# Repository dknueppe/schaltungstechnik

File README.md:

# Table of Contents

1.  [Aktiver Tiefpassfilter im Rahmen des Schaltungstechnik Praktikums](#org497d46e)
    1.  [Realisierung eines 1kHz Tiefpassfilter mit veränderlicher Verstärkung](#orgdd8e5d2)
    2.  [Bill of Materials](#org9c20808)

# Aktiver Tiefpassfilter im Rahmen des Schaltungstechnik Praktikums

## Realisierung eines 1kHz Tiefpassfilter mit veränderlicher Verstärkung

Der Filter nutzt eine Sallen-Key Topologie und kann mit verschiedenen Spannungsquellen betrieben werden.
Desweiteren lässt sich die Verstärkung über ein Potentiometer verstellen.

Der Jumper ist entsprechend der Spannungsversorgung zu setzen. Auf der Stellung **GND** wird das GND potential
zur Referenzspannung für den Verstärker, somit sollte eine symmetrische Spannungsversorgung genutzt werden.
Auf der Stellung **REF** wird eine interne Referenzspannung genutzt, es ist empfohlen das Spannungsquelle und
Signal in diesem Fall voneinander galvanisch getrennt sind.

## Bill of Materials

<table border="2" cellspacing="0" cellpadding="6" rules="groups" frame="hsides">

<colgroup>
<col  class="org-right" />

<col  class="org-left" />

<col  class="org-left" />

<col  class="org-left" />

<col  class="org-right" />

<col  class="org-left" />

<col  class="org-left" />
</colgroup>
<thead>
<tr>
<th scope="col" class="org-right">Pos</th>
<th scope="col" class="org-left">Item</th>
<th scope="col" class="org-left">Value</th>
<th scope="col" class="org-left">Package</th>
<th scope="col" class="org-right">Qty</th>
<th scope="col" class="org-left">Cost</th>
<th scope="col" class="org-left">Link</th>
</tr>
</thead>

<tbody>
<tr>
<td class="org-right">1</td>
<td class="org-left">Op-Amp</td>
<td class="org-left">ADA4610-2</td>
<td class="org-left">SOIC-8</td>
<td class="org-right">1</td>
<td class="org-left">2.04 €</td>
<td class="org-left">[@digikey](https://www.digikey.de/product-detail/de/analog-devices-inc/ADA4062-2ARZ/ADA4062-2ARZ-ND/1979393)</td>
</tr>

<tr>
<td class="org-right">2</td>
<td class="org-left">Capacitor</td>
<td class="org-left">10uF</td>
<td class="org-left">SMT 5x5.4</td>
<td class="org-right">2</td>
<td class="org-left">0.30 €</td>
<td class="org-left">[@digikey](https://www.digikey.de/product-detail/de/panasonic-electronic-components/EEE-1VA100WR/PCE3948CT-ND/766324)</td>
</tr>

<tr>
<td class="org-right">5</td>
<td class="org-left">Potentiometer</td>
<td class="org-left">100kΩ</td>
<td class="org-left">THT</td>
<td class="org-right">1</td>
<td class="org-left">0.71 €</td>
<td class="org-left">[@digikey](https://www.digikey.de/product-detail/de/bourns-inc/PTV09A-4020U-B104/PTV09A-4020U-B104-ND/3781131)</td>
</tr>

<tr>
<td class="org-right">3</td>
<td class="org-left">Pin Header</td>
<td class="org-left">Male</td>
<td class="org-left">THT 1x3</td>
<td class="org-right">3</td>
<td class="org-left">&#xa0;</td>
<td class="org-left">&#xa0;</td>
</tr>

<tr>
<td class="org-right">6</td>
<td class="org-left">Resistor</td>
<td class="org-left">47kΩ</td>
<td class="org-left">SMT 0603</td>
<td class="org-right">3</td>
<td class="org-left">&#xa0;</td>
<td class="org-left">&#xa0;</td>
</tr>

<tr>
<td class="org-right">7</td>
<td class="org-left">Resistor</td>
<td class="org-left">820kΩ</td>
<td class="org-left">SMT 0603</td>
<td class="org-right">1</td>
<td class="org-left">&#xa0;</td>
<td class="org-left">&#xa0;</td>
</tr>

<tr>
<td class="org-right">8</td>
<td class="org-left">Resistor</td>
<td class="org-left">3.3kΩ</td>
<td class="org-left">SMT 0603</td>
<td class="org-right">1</td>
<td class="org-left">&#xa0;</td>
<td class="org-left">&#xa0;</td>
</tr>

<tr>
<td class="org-right">9</td>
<td class="org-left">Capacitor</td>
<td class="org-left">100nF</td>
<td class="org-left">SMT 0603</td>
<td class="org-right">4</td>
<td class="org-left">&#xa0;</td>
<td class="org-left">&#xa0;</td>
</tr>

<tr>
<td class="org-right">10</td>
<td class="org-left">Capacitor</td>
<td class="org-left">1.2nF</td>
<td class="org-left">SMT 0603</td>
<td class="org-right">2</td>
<td class="org-left">&#xa0;</td>
<td class="org-left">&#xa0;</td>
</tr>
</tbody>
</table>

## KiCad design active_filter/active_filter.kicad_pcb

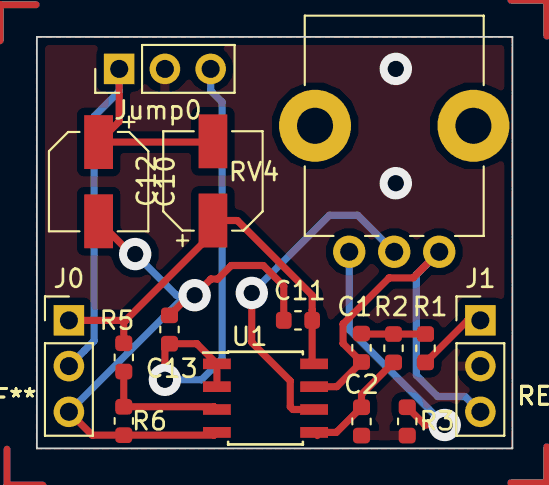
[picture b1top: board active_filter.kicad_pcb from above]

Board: 2 copper layers, 26.4 x 22.9 mm, 16 parts (0 on the bottom side), 12 nets.

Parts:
C1: 2.2n; C_0603_1608Metric
C2: 220p; C_0603_1608Metric
C10, C12: 10u; CP_Elec_5x5.4
C11, C13: 100n; C_0603_1608Metric
J0: Conn_01x03; PinHeader_1x03_P2.54mm_Vertical
J1: Conn_01x03_MountingPin; PinHeader_1x03_P2.54mm_Vertical
Jump0: Jumper_3_Bridged12; PinHeader_1x03_P2.54mm_Vertical
R1, R5, R6: 47k; R_0603_1608Metric
R2: 820k; R_0603_1608Metric
R3: 3.3k; R_0603_1608Metric
RV4: 100k; Potentiometer_Bourns_PTV09A-1_Single_Vertical
U1: ADA4062-2; SOIC-8_3.9x4.9mm_P1.27mm

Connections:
COM: C2.2, J1.2, Jump0.2, R3.2
GND: C10.1, C12.2, J0.2, Jump0.1
IN: J1.1, R1.1
unnamed: C1.2, R1.2, R2.1
unnamed: C2.1, R2.2, U1.5
unnamed: R3.1, RV4.3
unnamed: R5.2, R6.1, U1.3
unnamed: RV4.2, U1.6
OUT: C1.1, J1.3, RV4.1, U1.7
REF: C13.1, Jump0.3, U1.1, U1.2
VCC: C11.1, C12.1, J0.1, R5.1, U1.8
VEE: C10.2, C11.2, C13.2, J0.3, R6.2, U1.4

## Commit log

2018-08-15 added project: active_filter
2018-08-15 fixed wrongly filled area
2018-08-15 shortened some traces
2018-08-15 added gerber and bom
2018-08-15 SYNC:
2018-09-05 swapped op updated BoM
2018-09-06 added simulation
2018-09-06 updated gerber files
2018-09-21 V1.0
    Just a Mark to get back to eventually
2018-09-21 swapped some connectors added jumper
2018-09-21 changed parts checked design rules
2018-09-24 changed critical via
2018-09-24 Updated README and BOM
2018-09-24 updated pcb and bom
2018-09-24 deleted old stuff
2018-09-24 updated silkscreen
2018-09-24 fixed package for poti
2018-09-24 added power_flag symbols
2018-09-24 added second decoupling cap and swapped symbols
2018-09-25 corrected qty of caps
2018-09-25 added missing traces
2018-09-26 Passermarken und Gerber hinzugefügt
